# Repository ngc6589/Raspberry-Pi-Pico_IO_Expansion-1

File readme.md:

# Raspberry Pi Pico I/O Expansion Board

# この基板について

これは、Raspberry Pi Pico のピンを 2x20 のヘッダーピン（ピンソケット）に出す基板になります。ただし 2x20 ヘッダーピンは一部のピンを電源ピンに置き換えをしています。  
VBUS ピンは VSYS  
3V3_EN ピンは 3V3  
ADC_VREF は 3V3  

|Name|Pin|Pin|Name|
|---|---|---|---|
|GPIO0|1|40|VBUS → VSYS|
|GPIO1|2|39|VSYS|
|GND|3|38|GND|
|GPIO2|4|37|3V3_EN → 3V3|
|GPIO3|5|36|3V3|
|GPIO4|6|35|ADC_VREF → 3V3|
|GPIO5|7|34|GPIO28|
|GND|8|33|AGND|
|GPIO6|9|32|GPIO27|
|GPIO7|10|31|GPIO26|
|GPIO8|11|30|RUN|
|GPIO9|12|29|GPIO22|
|GND|13|28|GND|
|GPIO10|14|27|GPIO21|
|GPIO11|15|26|GPIO20|
|GPIO12|16|25|GPIO19|
|GPIO13|17|24|GPIO18|
|GND|18|23|GND|
|GPIO14|19|22|GPIO17|
|GPIO15|20|21|GPIO16|

# 回路図・ガーバーファイル
回路図は Schematic.pdf を参照してください。  
ガーバーファイルは KiCad フォルダーの Gerber-20230829 フォルダーを参照してください。

# Pico Probe 接続
基板端の U2 は Pico Probe の Raspberry Pi Pico が実装される場所です。gdb でデバッグをする時は実装してください。  
Pico Probe は使用しないけど、刺したまま使用するときは基板の JP1 ～ JP4 のジャンパーピンを抜くことで分離できます。

# 電源
Pico Probe 用 Raspberry Pi Pico とターゲット(動作用)の Raspberry Pi Pico の VSYS 端子は接続されています。なので USB ケーブルをどちらに挿しても（同時挿し含む）Raspberry Pi Pico 並びに、2x20 ヘッダピン・ヘッダソケットの VSYS ピンには電源が供給されます。  
VSYS は USB コネクタの VBUS からショットキーバリアダイオード通過後の端子になるため 5V よりかは若干低い電圧であることは理解下さい。  
  
3V3 はターゲット Raspberry Pi Pico の 3V3 端子から供給されます。Raspberry Pi Pico の基板に 3.3V DC/DC コンバーターが搭載されていますが、Raspberry Pi Pico Datasheet の記載には、3V3 のピンは 300mA 以下推奨とあります。

# 組み立て例

組み立て例は、Raspberry Pi Pico ボードをピンソケットで、横の I/O をピンヘッダーで出しました。
2x5 1.27mm ピッチヘッダピンは表面実装で、J-Link SWD 接続などで使うハーフピッチのコネクタ端子です。PicoProbe だけで使うときは実装不要です。

# 部品例

上記組み立て例の部品表は以下のようになります。

|部品番号|部品名|数量|通販アドレス|備考|
|---|---|---|---|---|
|U1, U2|ピンソケット (メス) 1×20 (20P)|4|https://akizukidenshi.com/catalog/g/gC-03077/||
|JP1～JP4|ピンヘッダ 1×2 (2P) (10個入)|1|https://akizukidenshi.com/catalog/g/gC-08593/||
|U1|ピンソケット(メス) 1×3(3P)|2|https://akizukidenshi.com/catalog/g/gC-10098/||
|J1, J2, J3|ピンヘッダ 2×20 (40P)|3|https://akizukidenshi.com/catalog/g/gC-00080/|
|JP1～JP4|ジャンパーピン赤(2.54mmピッチ) (25個入)|1|https://akizukidenshi.com/catalog/g/gP-03688/|
|SW1|タクトスイッチ（黄色）|1|https://akizukidenshi.com/catalog/g/gP-03650/|
|J6|コネクタ付コード 3P (青×3) 1mmピッチ|1|https://akizukidenshi.com/catalog/g/gC-11507/|
|J7|ピンヘッダ 2×5(10P) 表面実装用 1.27mmピッチ|1|https://akizukidenshi.com/catalog/g/gC-10904/|
|J4, J5|未実装||||

# 引用
Raspberry Pi PICO の KiCad ライブラリは https://github.com/ncarandini/KiCad-RP-Pico を利用しています。

# 使用例

## Raspberry Pi Pico
Raspberry Pi PIco は3ピンデバッグ端子にヘッダピンを付けて装着して下さい。

## Raspberry Pi Pico H
ヘッダピンがあらかじめ実装されている Raspberry Pi Pico H はデバッグ端子は1mm間隔のJST SHコネクタになっています。基板からSHコネクタの線を出して接続します

## Raspberry Pi Pico W
Raspberry Pi PIco 無線LAN付きは3ピンデバッグ端子にヘッダピンを付けて装着して下さい。

## Raspberry Pi Pico WH
ヘッダピン付き Raspberry Pi Pico HW は入手出来ていませんので写真はありませんが、Pico H 同様 JST SH コネクタでデバッグ端子に接続して下さい。

## SWD 接続のデバッガで使用する

2x5 ヘッダピンに SWD 接続可能なデバッガのケーブルを取り付けることで、違うデバッガを使用することができます。

**基板の SWD/SWCLK のジャンパは抜いてください。PicoProbe とショートしますので故障の原因となります。**

この接続でも PicoProbe は USB シリアルとして使用可能ですので、Raspberry Pi Pico の puts 出力などは PicoProbe 経由で受けられます。

# 頒布

https://www.em9system.com/?p=1047

にて在庫限りでピンソケット、ピンヘッダなど部品付きセットを頒布しています。

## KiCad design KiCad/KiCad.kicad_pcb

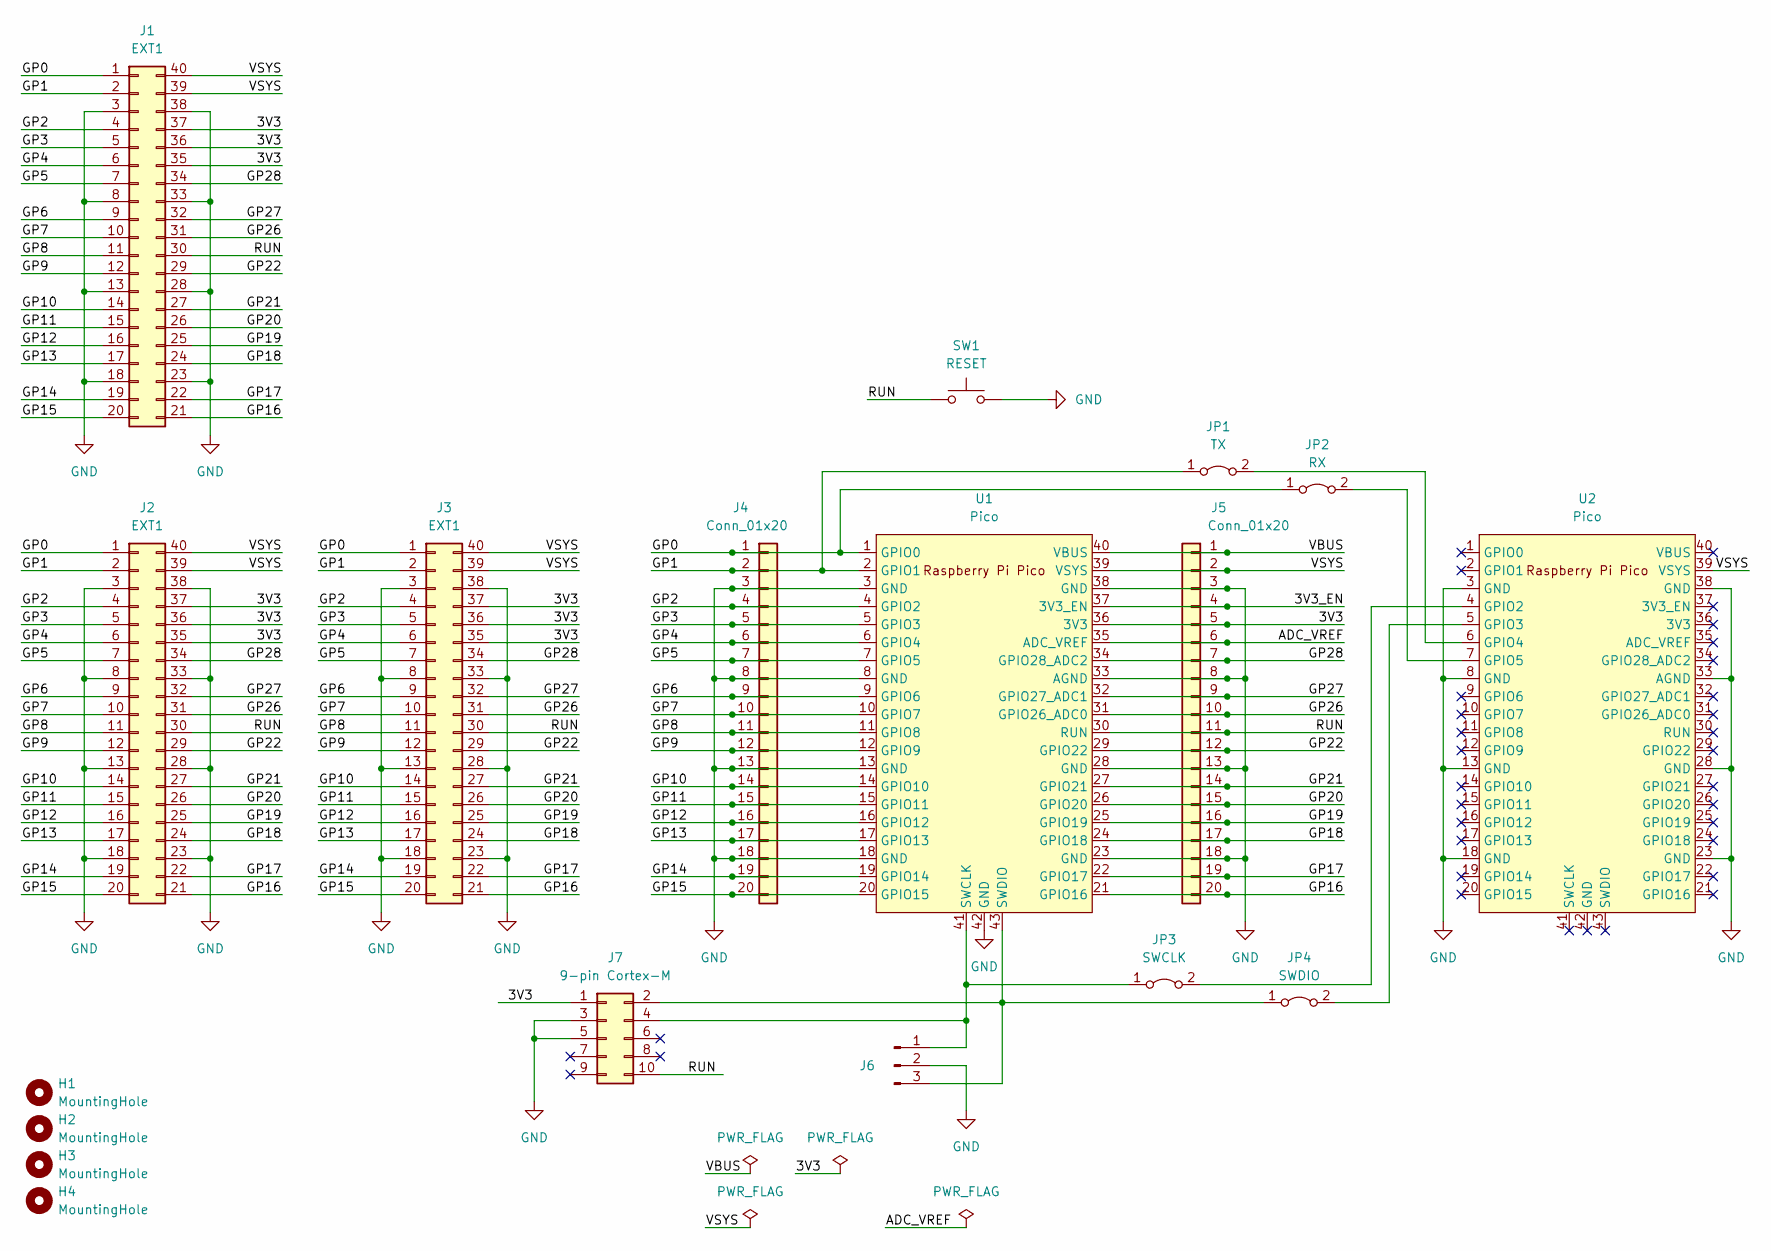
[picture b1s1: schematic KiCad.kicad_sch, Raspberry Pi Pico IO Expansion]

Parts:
H1, H2, H3, H4: MountingHole; MountingHole_3.2mm_M3
J1, J2, J3: EXT1; dualHeader
J4: Conn_01x20; leftHeader
J5: Conn_01x20; rightHeader
J6: Conn_01x03_Pin; PinHeader_1x03_P2.54mm_Vertical
J7: 9-pin Cortex-M; PinHeader_2x05_P1.27mm_Vertical_SMD
JP1: TX; PinHeader_1x02_P2.54mm_Vertical
JP2: RX; PinHeader_1x02_P2.54mm_Vertical
JP3: SWCLK; PinHeader_1x02_P2.54mm_Vertical
JP4: SWDIO; PinHeader_1x02_P2.54mm_Vertical
SW1: RESET; SW_PUSH_6mm
U1, U2: Pico; RPi_Pico_SMD_TH

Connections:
/3V3: J1.35, J1.36, J1.37, J2.35, J2.36, J2.37, J3.35, J3.36, J3.37, J5.5, J7.1, U1.36 (3V3)
/3V3_EN: J5.4, U1.37 (3V3_EN)
/ADC_VREF: J5.6, U1.35 (ADC_VREF)
/GP0: J1.1, J2.1, J3.1, J4.1, JP2.1 (A), U1.1 (GPIO0)
/GP1: J1.2, J2.2, J3.2, J4.2, JP1.1 (A), U1.2 (GPIO1)
/GP2: J1.4, J2.4, J3.4, J4.4, U1.4 (GPIO2)
/GP3: J1.5, J2.5, J3.5, J4.5, U1.5 (GPIO3)
/GP4: J1.6, J2.6, J3.6, J4.6, U1.6 (GPIO4)
/GP5: J1.7, J2.7, J3.7, J4.7, U1.7 (GPIO5)
/GP6: J1.9, J2.9, J3.9, J4.9, U1.9 (GPIO6)
/GP7: J1.10, J2.10, J3.10, J4.10, U1.10 (GPIO7)
/GP8: J1.11, J2.11, J3.11, J4.11, U1.11 (GPIO8)
/GP9: J1.12, J2.12, J3.12, J4.12, U1.12 (GPIO9)
/GP10: J1.14, J2.14, J3.14, J4.14, U1.14 (GPIO10)
/GP11: J1.15, J2.15, J3.15, J4.15, U1.15 (GPIO11)
/GP12: J1.16, J2.16, J3.16, J4.16, U1.16 (GPIO12)
/GP13: J1.17, J2.17, J3.17, J4.17, U1.17 (GPIO13)
/GP14: J1.19, J2.19, J3.19, J4.19, U1.19 (GPIO14)
/GP15: J1.20, J2.20, J3.20, J4.20, U1.20 (GPIO15)
/GP16: J1.21, J2.21, J3.21, J5.20, U1.21 (GPIO16)
/GP17: J1.22, J2.22, J3.22, J5.19, U1.22 (GPIO17)
/GP18: J1.24, J2.24, J3.24, J5.17, U1.24 (GPIO18)
/GP19: J1.25, J2.25, J3.25, J5.16, U1.25 (GPIO19)
/GP20: J1.26, J2.26, J3.26, J5.15, U1.26 (GPIO20)
/GP21: J1.27, J2.27, J3.27, J5.14, U1.27 (GPIO21)
/GP22: J1.29, J2.29, J3.29, J5.12, U1.29 (GPIO22)
/GP26: J1.31, J2.31, J3.31, J5.10, U1.31 (GPIO26_ADC0)
/GP27: J1.32, J2.32, J3.32, J5.9, U1.32 (GPIO27_ADC1)
/GP28: J1.34, J2.34, J3.34, J5.7, U1.34 (GPIO28_ADC2)
/RUN: J1.30, J2.30, J3.30, J5.11, J7.10, SW1.1, U1.30 (RUN)
/VBUS: J5.1, U1.40 (VBUS)
/VSYS: J1.39, J1.40, J2.39, J2.40, J3.39, J3.40, J5.2, U1.39 (VSYS), U2.39 (VSYS)
GND: J1.3, J1.8, J1.13, J1.18, J1.23, J1.28, J1.33, J1.38, J2.3, J2.8, J2.13, J2.18, J2.23, J2.28, J2.33, J2.38, J3.3, J3.8, J3.13, J3.18, J3.23, J3.28, J3.33, J3.38, J4.3, J4.8, J4.13, J4.18, J5.3, J5.8, J5.13, J5.18, J6.2, J7.3, J7.5, SW1.2, U1.3 (GND), U1.8 (GND), U1.13 (GND), U1.18 (GND), U1.23 (GND), U1.28 (GND), U1.33 (AGND), U1.38 (GND), U1.42 (GND), U2.3 (GND), U2.8 (GND), U2.13 (GND), U2.18 (GND), U2.23 (GND), U2.28 (GND), U2.33 (AGND), U2.38 (GND)
unnamed: J6.1, J7.4, JP3.1 (A), U1.41 (SWCLK)
unnamed: J6.3, J7.2, JP4.1 (A), U1.43 (SWDIO)
unnamed: JP1.2 (B), U2.6 (GPIO4)
unnamed: JP2.2 (B), U2.7 (GPIO5)
unnamed: JP3.2 (B), U2.4 (GPIO2)
unnamed: JP4.2 (B), U2.5 (GPIO3)

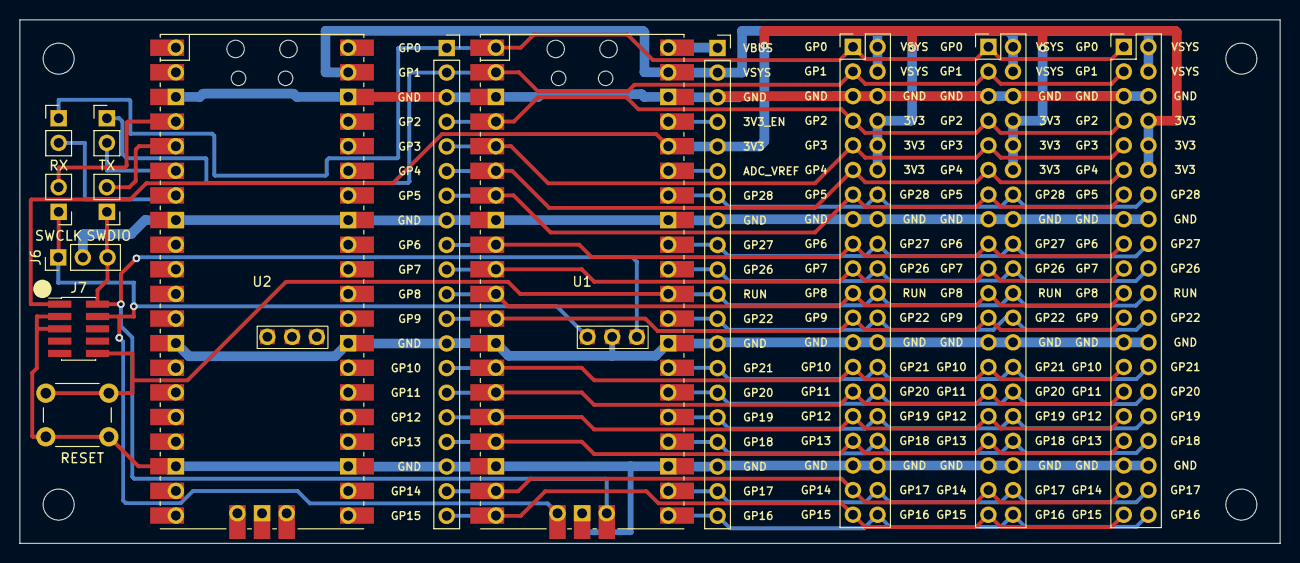
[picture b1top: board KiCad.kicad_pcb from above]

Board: 2 copper layers, 130.0 x 54.0 mm, 18 parts (0 on the bottom side), 39 nets.

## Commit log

2022-10-18 add files
2022-10-18 modify photo
2022-10-18 add gitignore
2023-06-03 update new PCB
2023-09-07 update board revision
2023-09-07 update material
